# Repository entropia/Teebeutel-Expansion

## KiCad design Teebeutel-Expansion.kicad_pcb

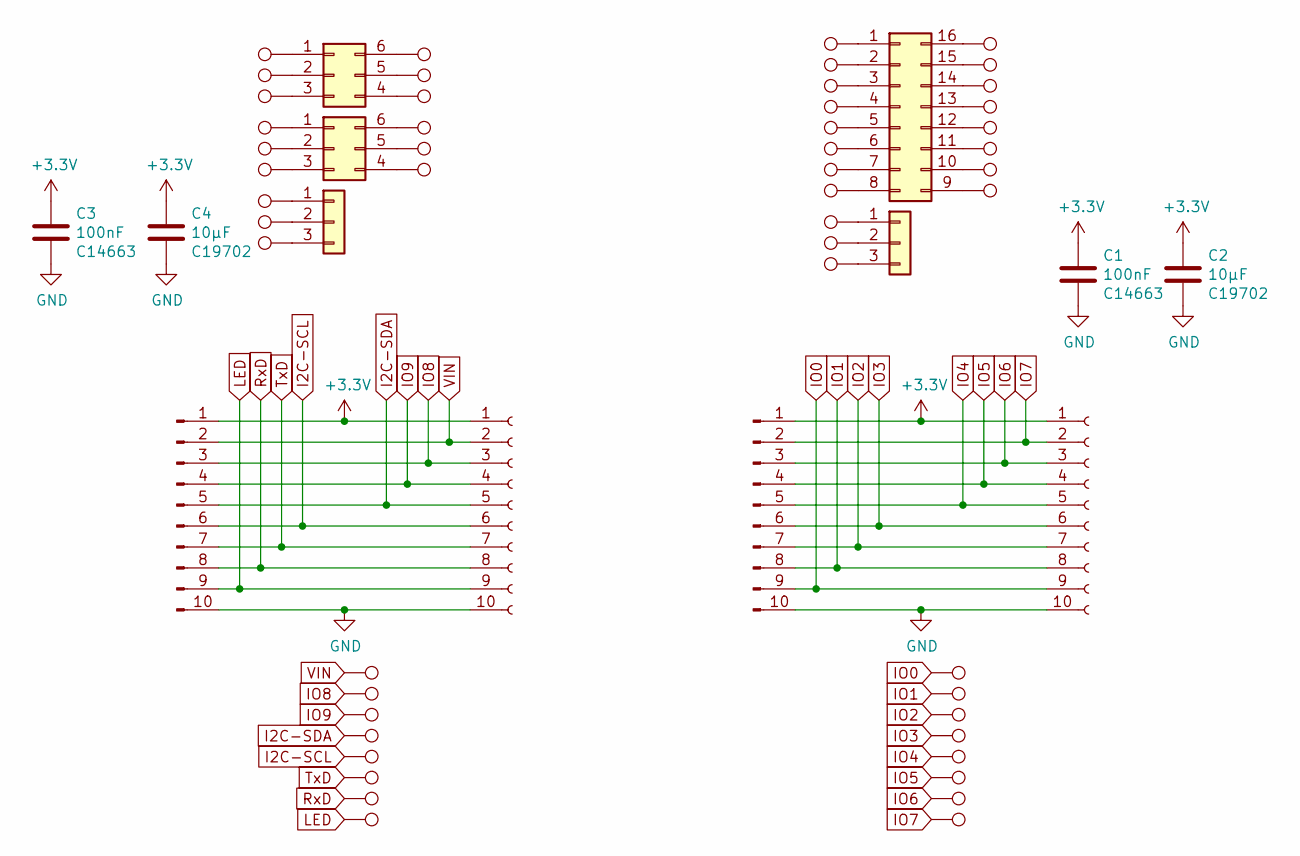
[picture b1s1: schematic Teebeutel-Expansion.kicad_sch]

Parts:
C1, C3: 100nF; C_0603_1608Metric; LCSC C14663
C2, C4: 10µF; C_0603_1608Metric; LCSC C19702
J1, J3: Conn_01x10_Male; PinHeader_1x10_P2.54mm_Vertical
J2, J4: Conn_01x10_Female; PinSocket_1x10_P2.54mm_Vertical
J5, J6: Conn_02x03_Counter_Clockwise; SOT-23-6_Handsoldering
J7, J8: Conn_01x03; SOT-23
J9: Conn_02x08_Counter_Clockwise; SOP-16_4.55x10.3mm_P1.27mm
TP1, TP2, TP3, TP4, TP5, TP6, TP7, TP8, TP9, TP10, TP11, TP12, TP13, TP14, TP15, TP16, TP17, TP18, TP19, TP20, TP21, TP22, TP23, TP24, TP25, TP26, TP27, TP28, TP29, TP30, TP31, TP32, TP33, TP34, TP35, TP36, TP37, TP38, TP39, TP40, TP41, TP42, TP43, TP44, TP45, TP46, TP47, TP48, TP49, TP50: TestPoint; TestPoint_THTPad_D1.5mm_Drill0.7mm

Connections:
+3V3: C1.1, C2.1, C3.1, C4.1, J1.1, J2.1, J3.1, J4.1
GND: C1.2, C2.2, C3.2, C4.2, J1.10, J2.10, J3.10, J4.10
I2C-SCL: J1.6, J2.6, TP5.1
I2C-SDA: J1.5, J2.5, TP4.1
IO0: J3.9, J4.9, TP16.1
IO1: J3.8, J4.8, TP15.1
IO2: J3.7, J4.7, TP14.1
IO3: J3.6, J4.6, TP13.1
IO4: J3.5, J4.5, TP12.1
IO5: J3.4, J4.4, TP11.1
IO6: J3.3, J4.3, TP10.1
IO7: J3.2, J4.2, TP9.1
IO8: J1.3, J2.3, TP2.1
IO9: J1.4, J2.4, TP3.1
LED: J1.9, J2.9, TP8.1
unnamed: J5.1, TP17.1
unnamed: J5.2, TP18.1
unnamed: J5.3, TP19.1
unnamed: J5.4, TP25.1
unnamed: J5.5, TP24.1
unnamed: J5.6, TP23.1
unnamed: J6.1, TP20.1
unnamed: J6.2, TP21.1
unnamed: J6.3, TP22.1
unnamed: J6.4, TP28.1
unnamed: J6.5, TP27.1
unnamed: J6.6, TP26.1
unnamed: J7.1, TP29.1
unnamed: J7.2, TP30.1
unnamed: J7.3, TP31.1
unnamed: J8.1, TP32.1
unnamed: J8.2, TP33.1
unnamed: J8.3, TP34.1
unnamed: J9.1, TP35.1
unnamed: J9.2, TP36.1
unnamed: J9.3, TP37.1
unnamed: J9.4, TP38.1
unnamed: J9.5, TP39.1
unnamed: J9.6, TP40.1
unnamed: J9.7, TP41.1
unnamed: J9.8, TP42.1
unnamed: J9.9, TP50.1
unnamed: J9.10, TP49.1
unnamed: J9.11, TP48.1
unnamed: J9.12, TP47.1
unnamed: J9.13, TP46.1
unnamed: J9.14, TP45.1
unnamed: J9.15, TP44.1
unnamed: J9.16, TP43.1
RxD: J1.8, J2.8, TP7.1
TxD: J1.7, J2.7, TP6.1
VIN: J1.2, J2.2, TP1.1

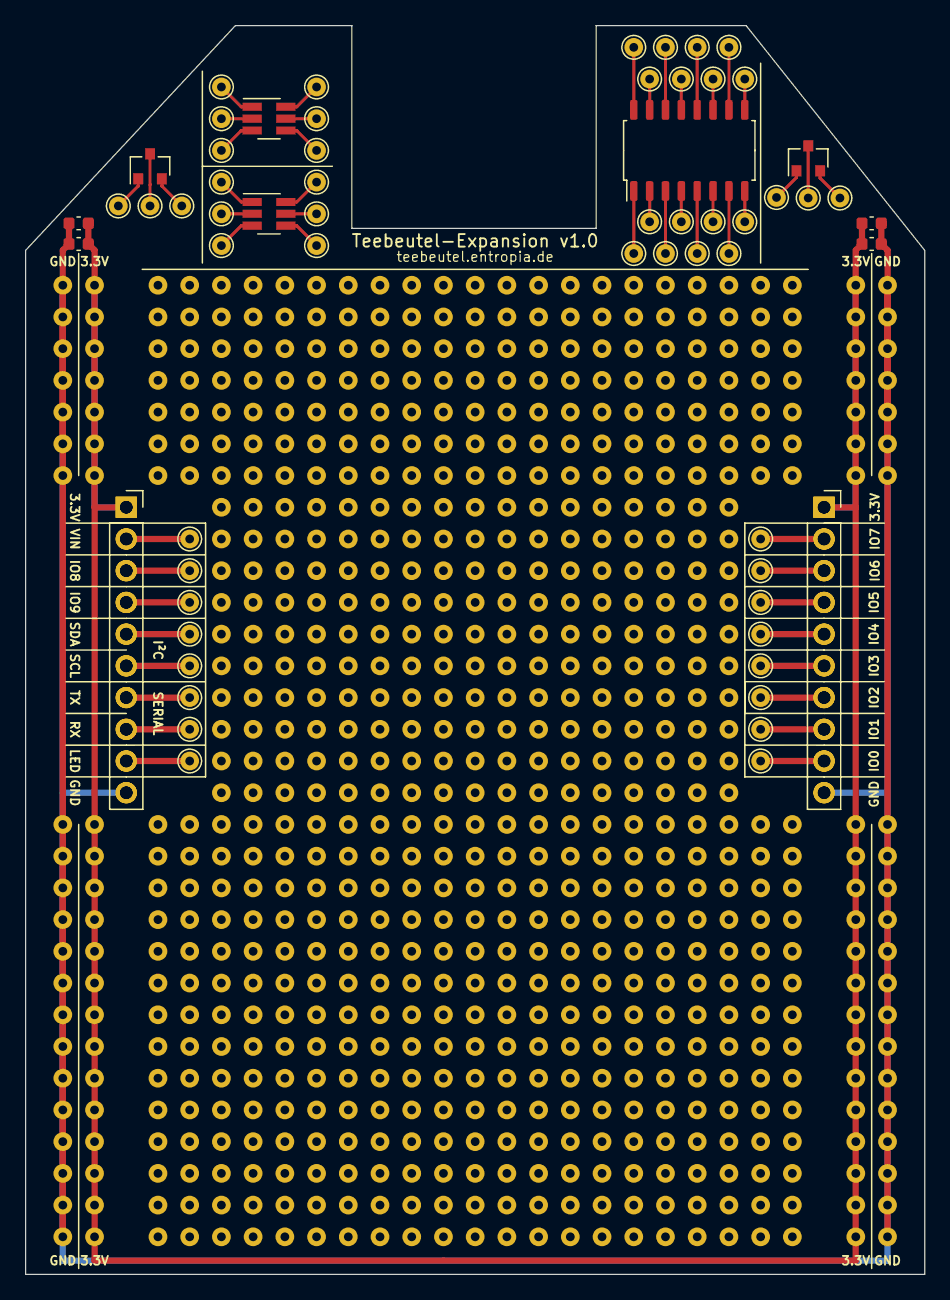
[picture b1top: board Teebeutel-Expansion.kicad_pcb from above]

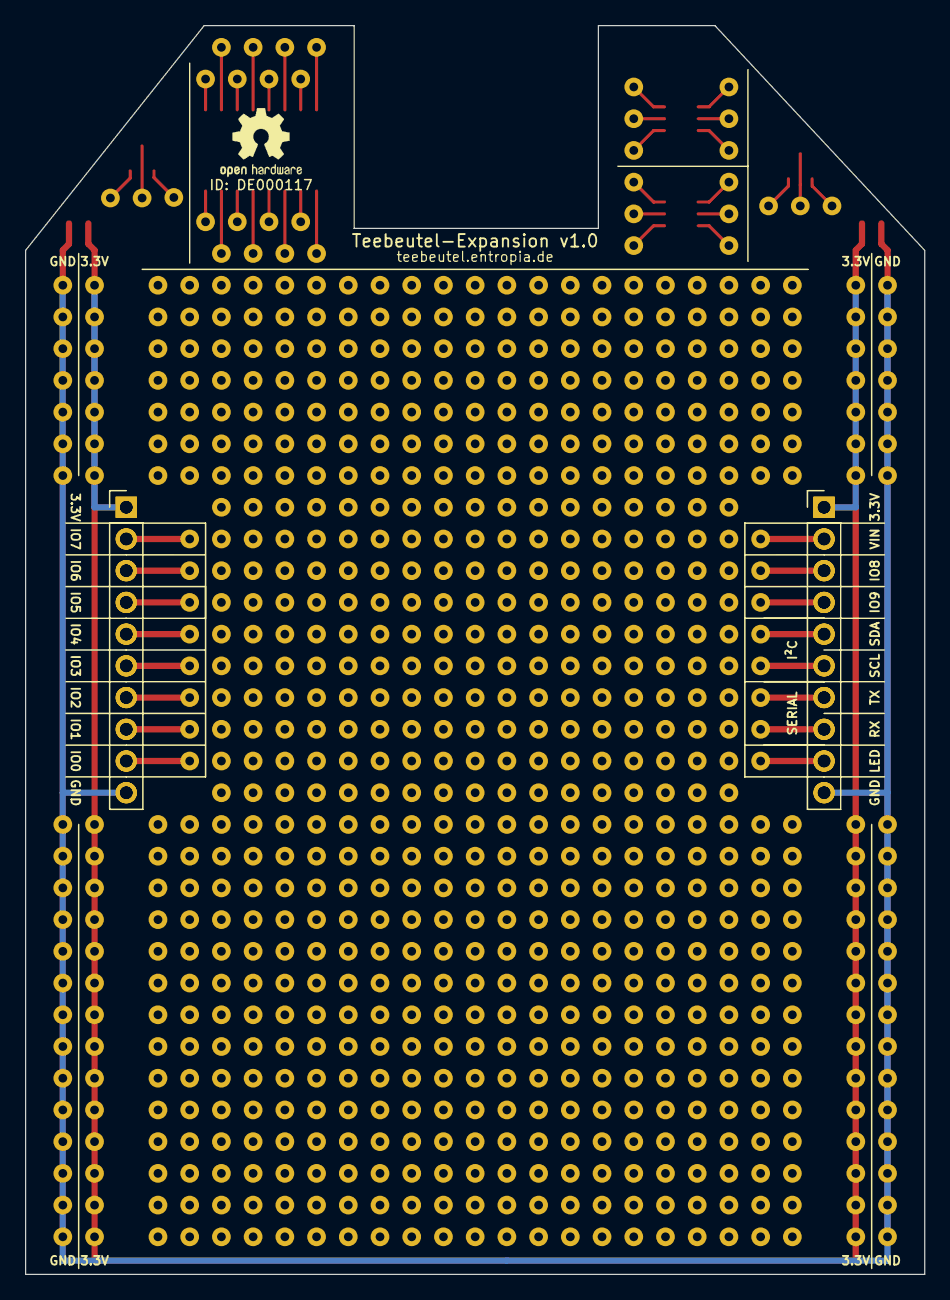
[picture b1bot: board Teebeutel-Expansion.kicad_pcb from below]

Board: 2 copper layers, 72.0 x 100.0 mm, 63 parts (2 on the bottom side), 52 nets.

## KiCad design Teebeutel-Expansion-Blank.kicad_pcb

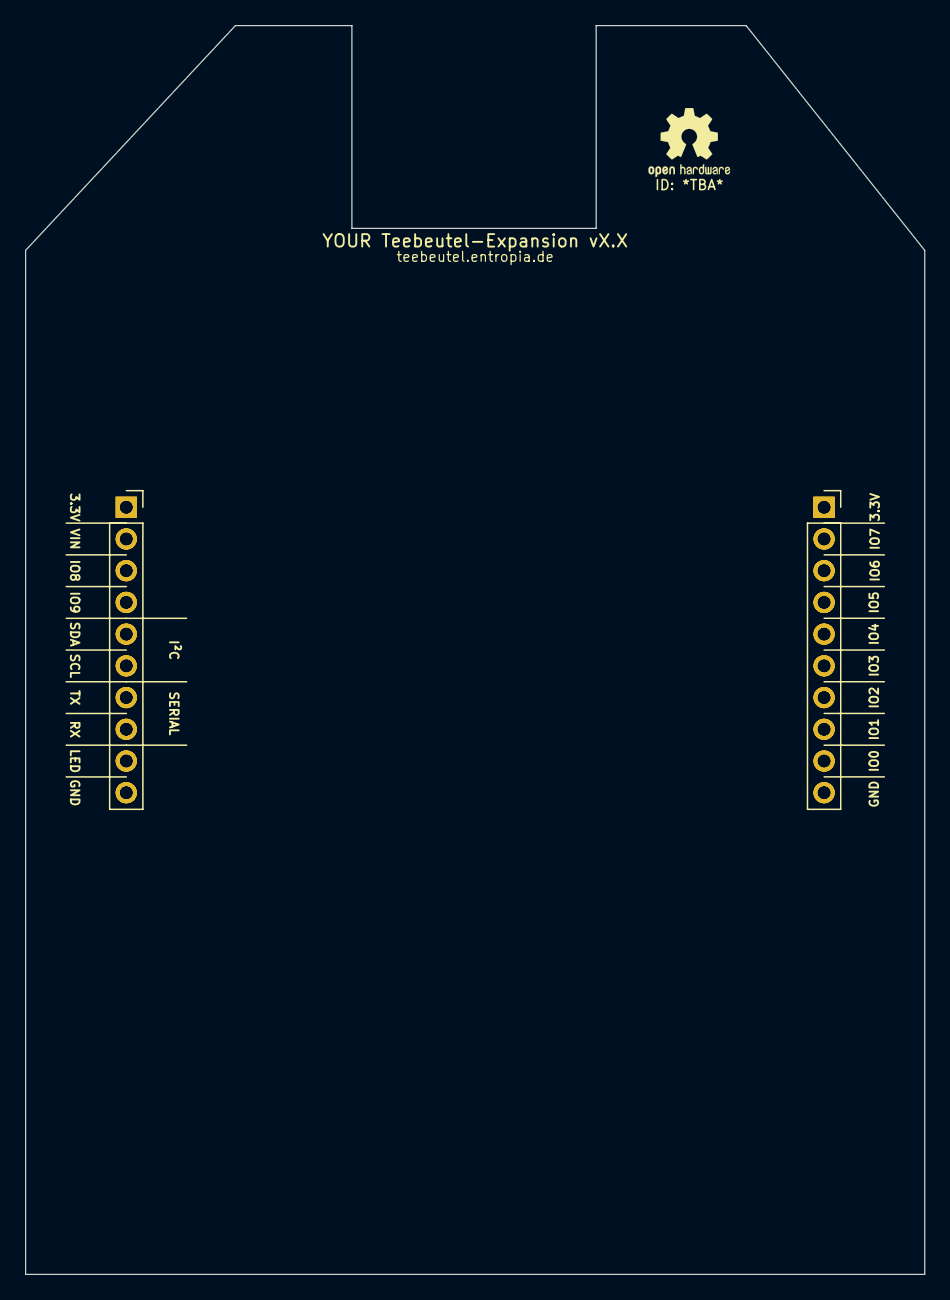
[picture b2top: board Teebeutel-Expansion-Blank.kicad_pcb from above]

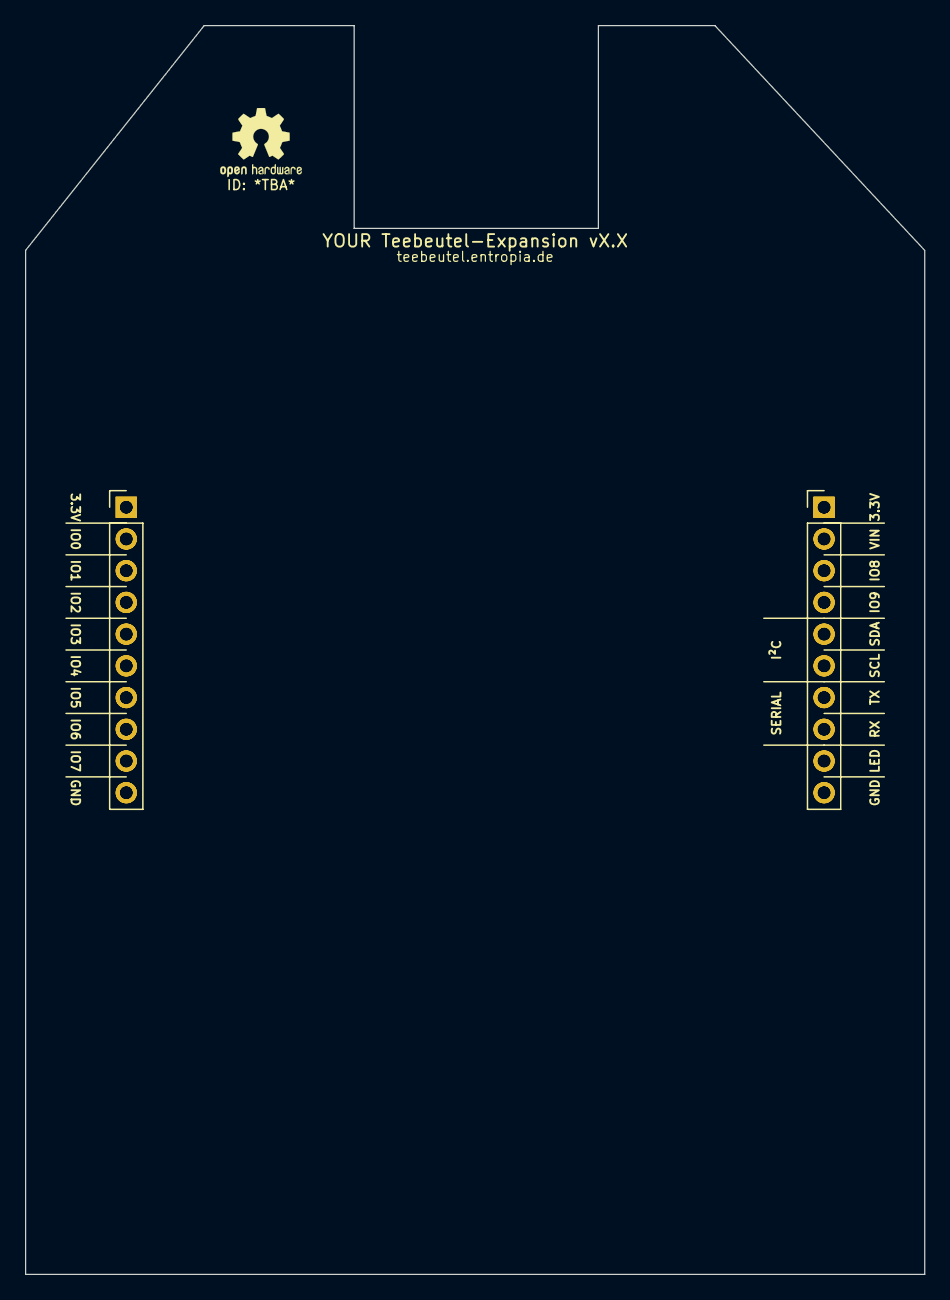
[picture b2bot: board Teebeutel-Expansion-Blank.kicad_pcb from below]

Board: 2 copper layers, 72.0 x 100.0 mm, 4 parts (2 on the bottom side), 18 nets, no tracks yet.

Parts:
J1, J3: Conn_01x10_Male; PinHeader_1x10_P2.54mm_Vertical
J2, J4: Conn_01x10_Female; PinSocket_1x10_P2.54mm_Vertical

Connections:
+3V3: J1.1, J2.1, J3.1, J4.1
GND: J1.10, J2.10, J3.10, J4.10
I2C-SCL: J1.6, J2.6
I2C-SDA: J1.5, J2.5
IO0: J3.9, J4.9
IO1: J3.8, J4.8
IO2: J3.7, J4.7
IO3: J3.6, J4.6
IO4: J3.5, J4.5
IO5: J3.4, J4.4
IO6: J3.3, J4.3
IO7: J3.2, J4.2
IO8: J1.3, J2.3
IO9: J1.4, J2.4
LED: J1.9, J2.9
RxD: J1.8, J2.8
TxD: J1.7, J2.7
VIN: J1.2, J2.2

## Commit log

2021-12-20 docs: add README
2021-12-20 chore: add CONTRIBUTING
2021-12-20 docs: initial commit
2021-12-24 docs(): Update documentation
2021-12-28 chore: Add CONTRIBUTING.md
2021-12-29 chore: cleanup and update to KiCad6
2021-12-31 chore: Update labels
2022-02-19 typo(): Add newline
2022-02-23 workflow: Trigger documentation updates automatically
2022-02-23 docs: Update version name
2022-02-24 pcb: Add GERBER config
2022-02-24 docs: Add stripboard expansion render

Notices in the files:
Teebeutel-Expansion-Blank.kicad_pcb:
License: CERN-OHL-S
Please remember to publish your Expansion under an OSHW-License!
